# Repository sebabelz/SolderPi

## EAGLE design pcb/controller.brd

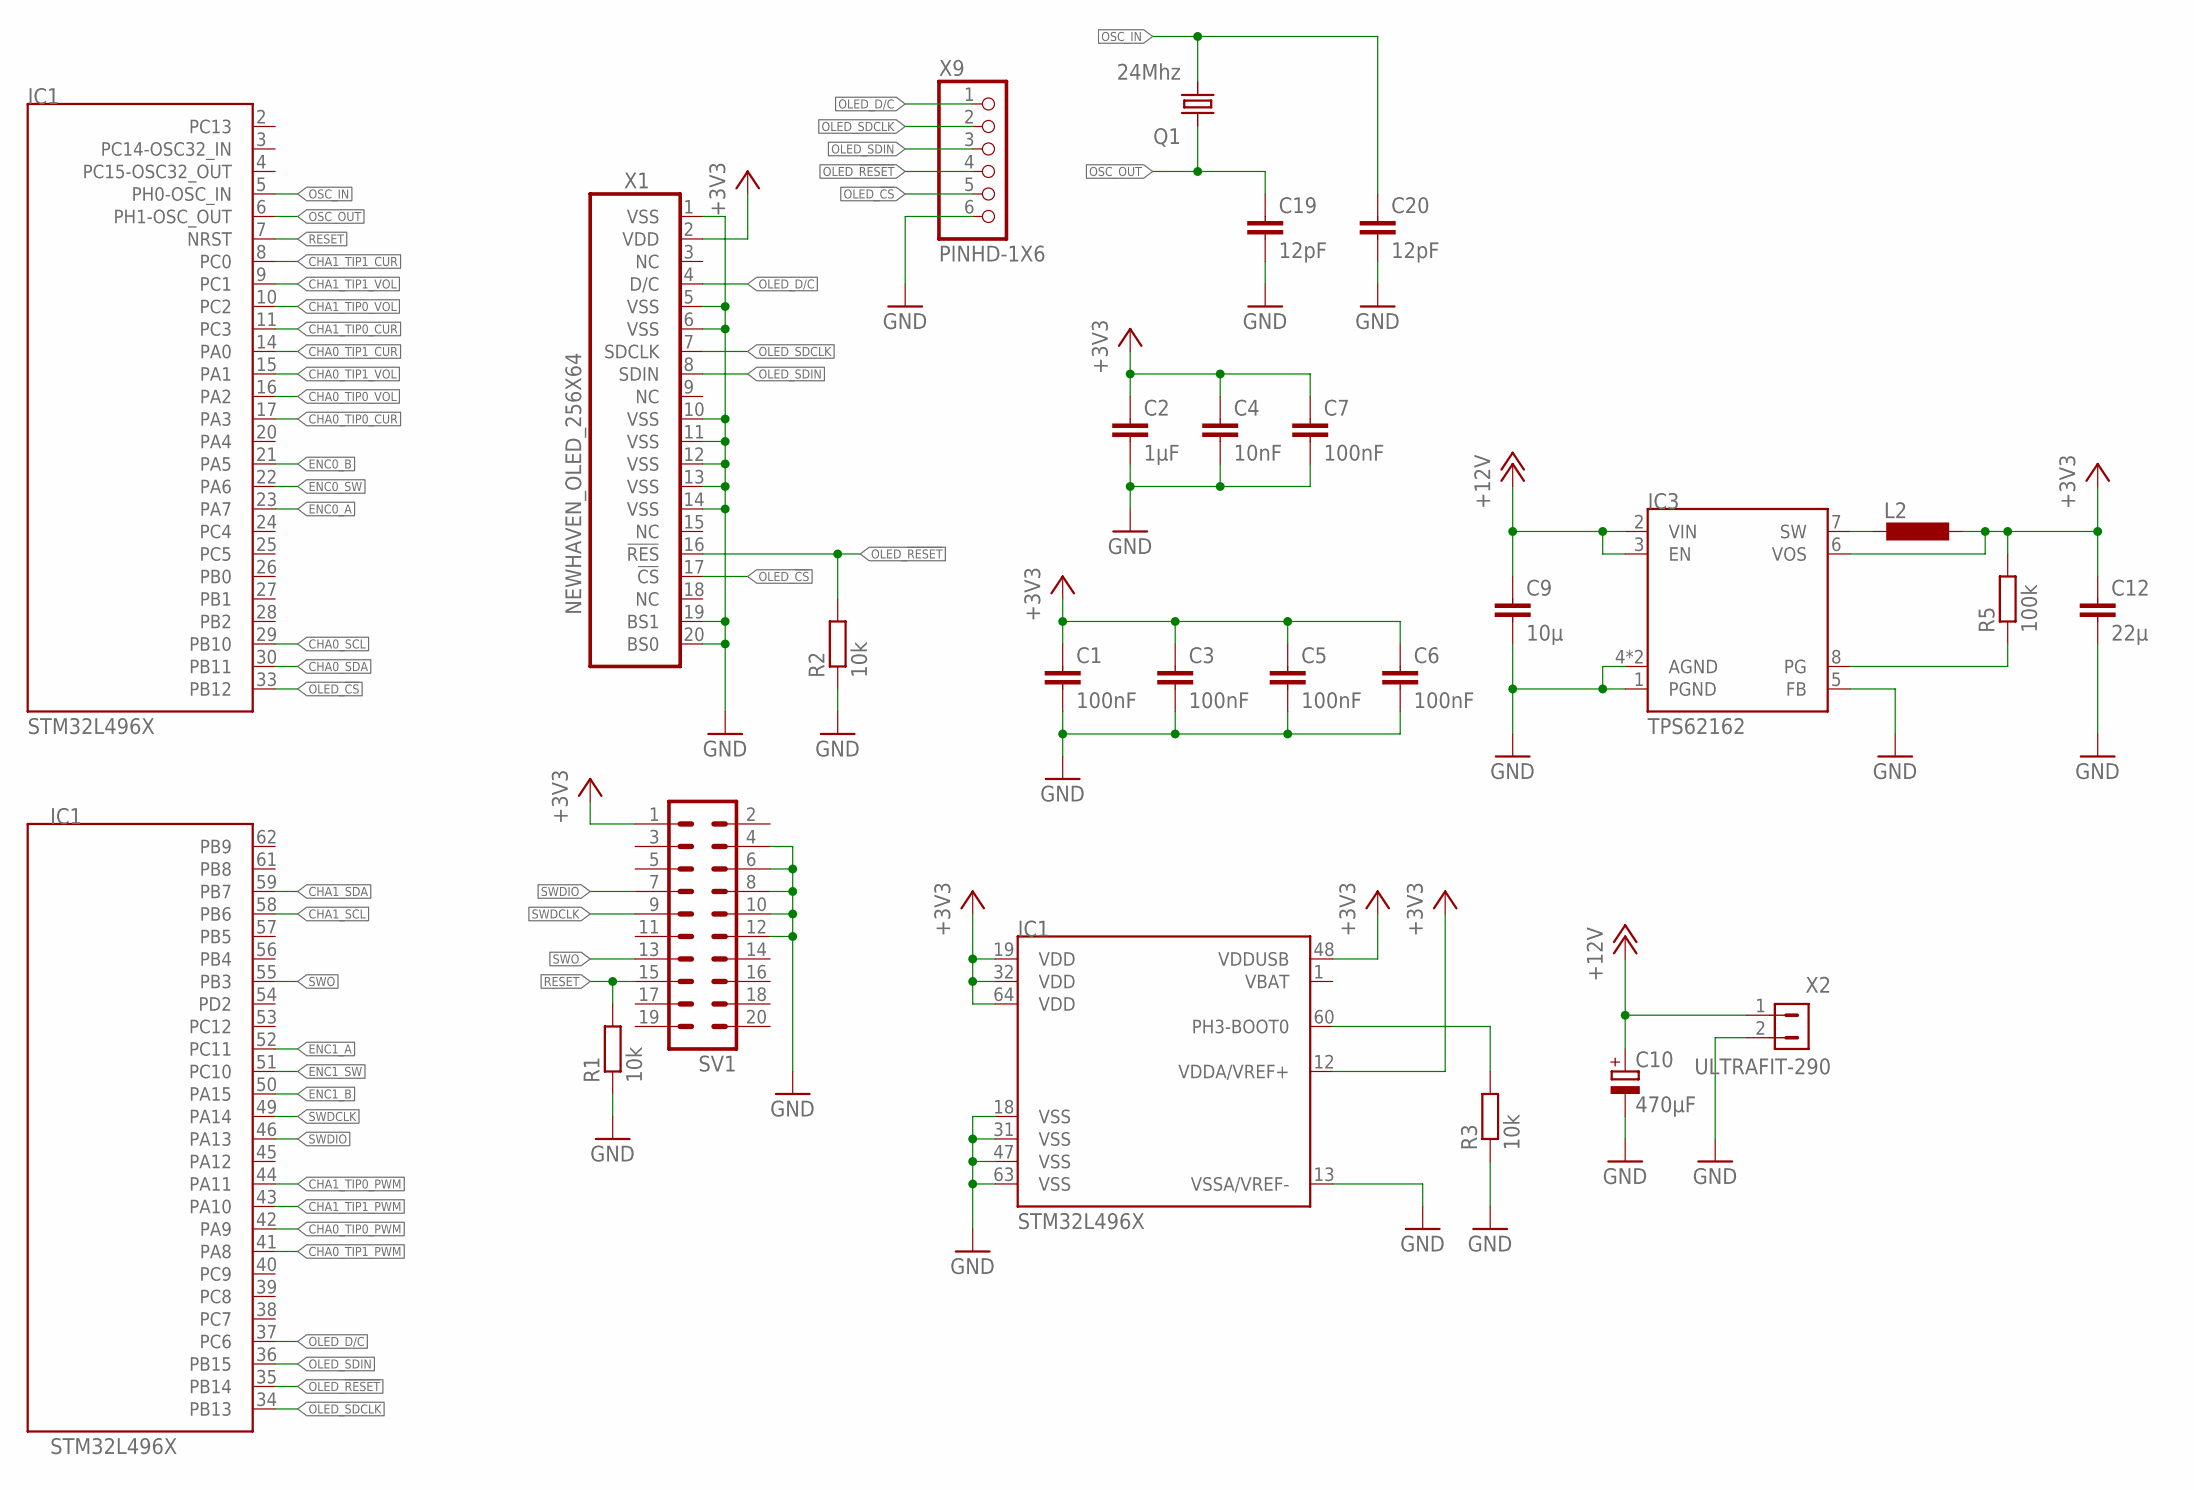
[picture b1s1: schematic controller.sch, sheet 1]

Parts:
C1, C3, C5, C6, C7: 100nF; C0402
C2: 1µF; C0402
C4: 10nF; C0402
C9: 10µ; C0805
C10: 470µF; C_EEEFK-10X10
C12: 22µ; C0805
C19, C20: 12pF; C0603
IC1: STM32L496X; TQFP64-10X10
IC3: TPS62162; WSON8
L2: VLF3012S; VLF3012ST
Q1: 24Mhz; HCR2520
R1, R2, R3: 10k; R0603
R5: 100k; R0603
SV1: ML20
X1: NEWHAVEN_OLED_256X64
X2: ULTRAFIT-290; ULTRAFIT-2-90
X9: PINHD-1X6; 1X06

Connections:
3V3_PG: IC3.8 (PG), R5.1
3V3_SW: IC3.7 (SW), L2.2
+3V3: C1.1, C2.1, C3.1, C4.1, C5.1, C6.1, C7.1, C12.1, IC1.12 (VDDA/VREF+), IC1.19 (VDD), IC1.32 (VDD), IC1.48 (VDDUSB), IC1.64 (VDD), IC3.6 (VOS), L2.1, R5.2, SV1.1, X1.2 (VDD); also elsewhere on the board
+12V: C9.1, C10.+, IC3.2 (VIN), IC3.3 (EN), X2.1; also elsewhere on the board
BOOT0: IC1.60 (PH3-BOOT0), R3.2
CHA0_SCL: IC1.29 (PB10); also elsewhere on the board
CHA0_SDA: IC1.30 (PB11); also elsewhere on the board
CHA0_TIP0_CUR: IC1.17 (PA3); also elsewhere on the board
CHA0_TIP0_PWM: IC1.42 (PA9); also elsewhere on the board
CHA0_TIP0_VOL: IC1.16 (PA2); also elsewhere on the board
CHA0_TIP1_CUR: IC1.14 (PA0); also elsewhere on the board
CHA0_TIP1_PWM: IC1.41 (PA8); also elsewhere on the board
CHA0_TIP1_VOL: IC1.15 (PA1); also elsewhere on the board
CHA1_SCL: IC1.58 (PB6); also elsewhere on the board
CHA1_SDA: IC1.59 (PB7); also elsewhere on the board
CHA1_TIP0_CUR: IC1.11 (PC3); also elsewhere on the board
CHA1_TIP0_PWM: IC1.44 (PA11); also elsewhere on the board
CHA1_TIP0_VOL: IC1.10 (PC2); also elsewhere on the board
CHA1_TIP1_CUR: IC1.8 (PC0); also elsewhere on the board
CHA1_TIP1_PWM: IC1.43 (PA10); also elsewhere on the board
CHA1_TIP1_VOL: IC1.9 (PC1); also elsewhere on the board
ENC0_A: IC1.23 (PA7); also elsewhere on the board
ENC0_B: IC1.21 (PA5); also elsewhere on the board
ENC0_SW: IC1.22 (PA6); also elsewhere on the board
ENC1_A: IC1.52 (PC11); also elsewhere on the board
ENC1_B: IC1.50 (PA15); also elsewhere on the board
ENC1_SW: IC1.51 (PC10); also elsewhere on the board
GND: C1.2, C2.2, C3.2, C4.2, C5.2, C6.2, C7.2, C9.2, C10.-, C12.2, C19.2, C20.2, IC1.13 (VSSA/VREF-), IC1.18 (VSS), IC1.31 (VSS), IC1.47 (VSS), IC1.63 (VSS), IC3.1 (PGND), IC3.4 (AGND), IC3.5 (FB), IC3.GND (AGND), R1.1, R2.1, R3.1, SV1.4, SV1.6, SV1.8, SV1.10, SV1.12, X1.1 (VSS), X1.5 (VSS), X1.6 (VSS), X1.10 (VSS), X1.11 (VSS), X1.12 (VSS), X1.13 (VSS), X1.14 (VSS), X1.19 (BS1), X1.20 (BS0), X2.2, X9.6; also elsewhere on the board
OLED_!CS: IC1.33 (PB12), X1.17 (!CS), X9.5
OLED_!RESET: IC1.35 (PB14), R2.2, X1.16 (!RES), X9.4
OLED_D/C: IC1.37 (PC6), X1.4 (D/C), X9.1
OLED_SDCLK: IC1.34 (PB13), X1.7 (SDCLK), X9.2
OLED_SDIN: IC1.36 (PB15), X1.8 (SDIN), X9.3
OSC_IN: C20.1, IC1.5 (PH0-OSC_IN), Q1.1
OSC_OUT: C19.1, IC1.6 (PH1-OSC_OUT), Q1.2
RESET: IC1.7 (NRST), R1.2, SV1.15
SWDCLK: IC1.49 (PA14), SV1.9
SWDIO: IC1.46 (PA13), SV1.7
SWO: IC1.55 (PB3), SV1.13

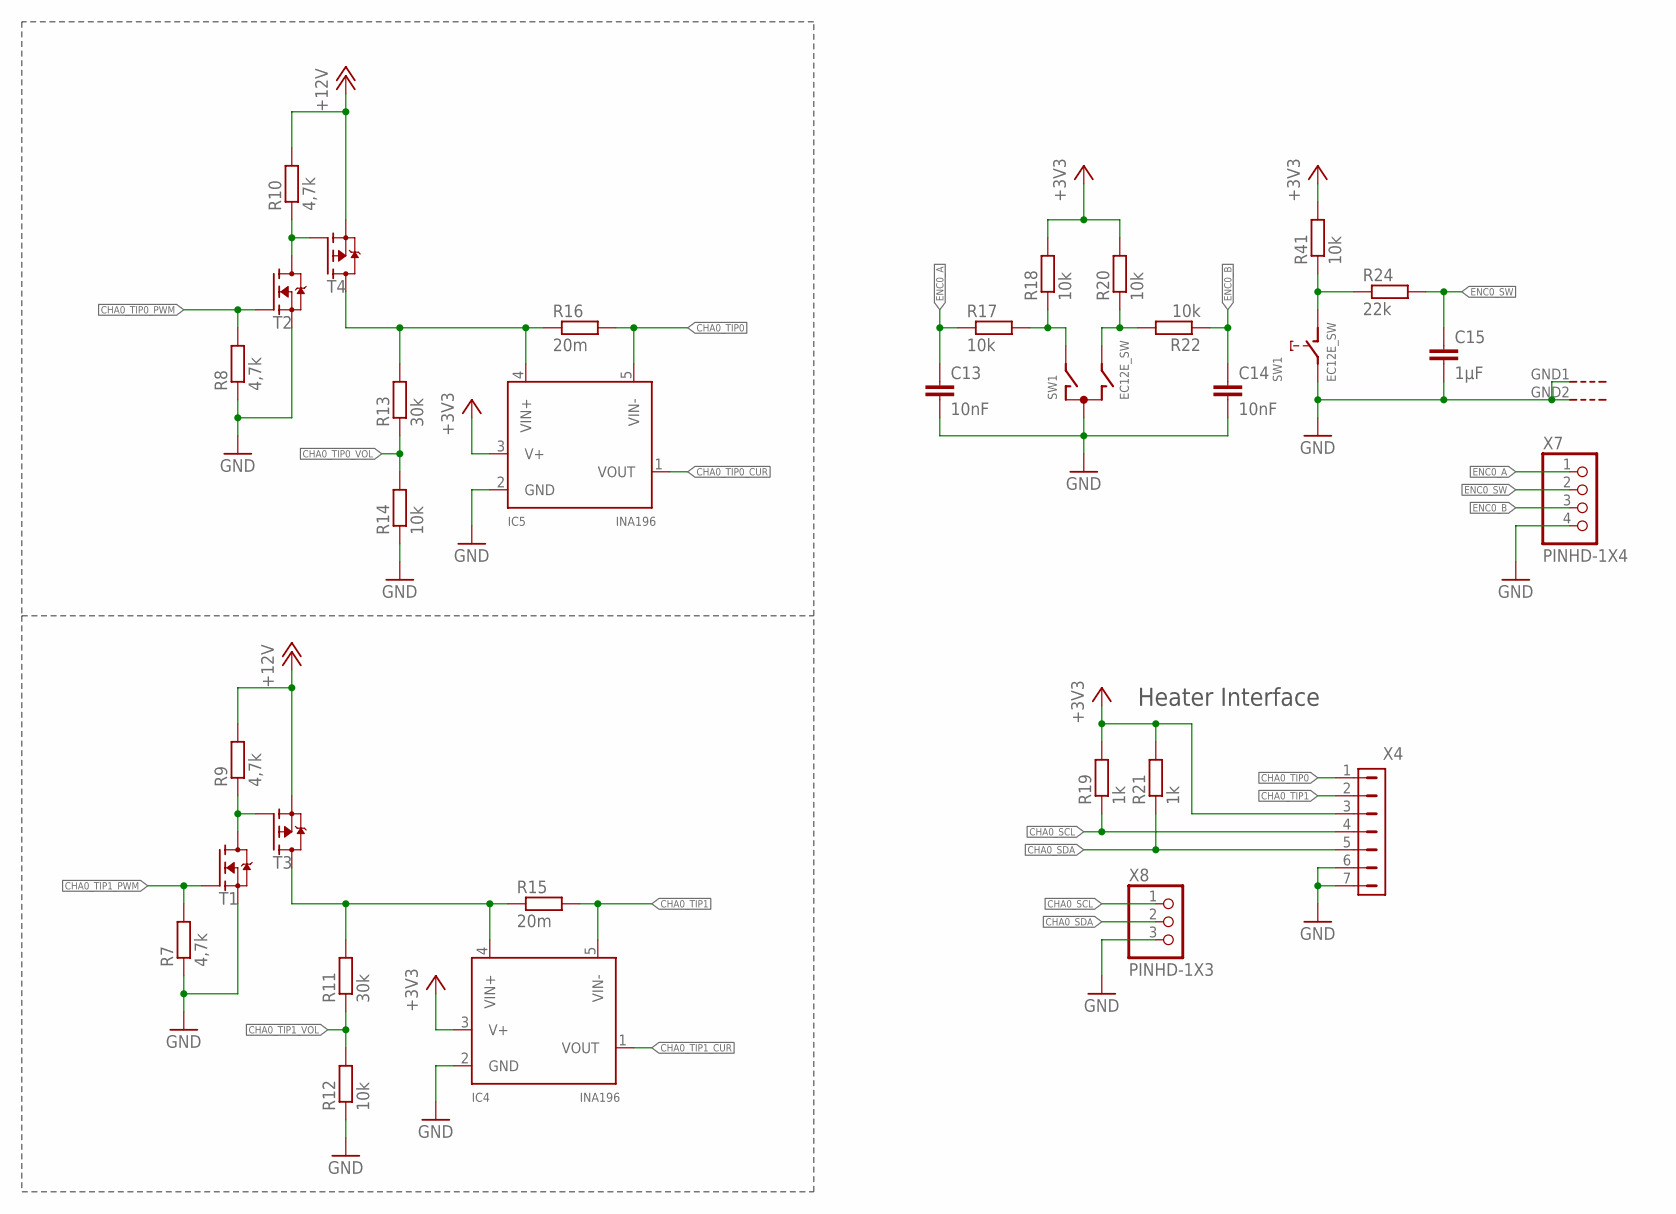
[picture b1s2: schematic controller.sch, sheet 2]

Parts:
C13, C14: 10nF; C0805
C15: 1µF; C0805
IC4, IC5: INA196; SOT23-5L
R7, R8, R9, R10: 4,7k; R0805
R11, R13: 30k; R0603
R12, R14: 10k; R0603
R15, R16: 20m; R2010
R17, R18, R20, R22, R41: 10k; R0805
R19, R21: 1k; R0603
R24: 22k; R0805
SW1: EC12E_SW; ALPS_EC12E_SW
T1, T2: NVR4003NT3G; SOT23
T3, T4: IRF7416; SO8
X4: NANOFIT-7
X7: PINHD-1X4; 1X04
X8: PINHD-1X3; 1X03

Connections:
+3V3: IC4.3 (V+), IC5.3 (V+), R18.2, R19.2, R20.2, R21.2, R41.2, X4.3; also elsewhere on the board
+12V: R9.2, R10.2, T3.1 (S), T3.2 (S), T3.3 (S), T4.1 (S), T4.2 (S), T4.3 (S); also elsewhere on the board
CHA0_SCL: R19.1, X4.4, X8.1; also elsewhere on the board
CHA0_SDA: R21.1, X4.5, X8.2; also elsewhere on the board
CHA0_TIP0: IC5.5 (VIN-), R16.2, X4.1
CHA0_TIP0_CUR: IC5.1 (VOUT); also elsewhere on the board
CHA0_TIP0_PWM: R8.2, T2.1 (G); also elsewhere on the board
CHA0_TIP0_PWM_D: R10.1, T2.3 (D), T4.4 (G)
CHA0_TIP0_SEN: IC5.4 (VIN+), R13.2, R16.1, T4.5 (D), T4.6 (D), T4.7 (D), T4.8 (D)
CHA0_TIP0_VOL: R13.1, R14.2; also elsewhere on the board
CHA0_TIP1: IC4.5 (VIN-), R15.2, X4.2
CHA0_TIP1_CUR: IC4.1 (VOUT); also elsewhere on the board
CHA0_TIP1_PWM: R7.2, T1.1 (G); also elsewhere on the board
CHA0_TIP1_PWM_D: R9.1, T1.3 (D), T3.4 (G)
CHA0_TIP1_SEN: IC4.4 (VIN+), R11.2, R15.1, T3.5 (D), T3.6 (D), T3.7 (D), T3.8 (D)
CHA0_TIP1_VOL: R11.1, R12.2; also elsewhere on the board
ENC0_A: C13.1, R17.1, X7.1; also elsewhere on the board
ENC0_A_UNFIL: R17.2, R18.1, SW1.A
ENC0_B: C14.1, R22.1, X7.3; also elsewhere on the board
ENC0_B_UNFIL: R20.1, R22.2, SW1.B
ENC0_SW: C15.1, R24.2, X7.2; also elsewhere on the board
ENC0_SW_R: R24.1, R41.1, SW1.D (1)
GND: C13.2, C14.2, C15.2, IC4.2 (GND), IC5.2 (GND), R7.1, R8.1, R12.1, R14.1, SW1.C, SW1.E (2), SW1.GND1 (G), SW1.GND2 (G), T1.2 (S), T2.2 (S), X4.6, X4.7, X7.4, X8.3; also elsewhere on the board

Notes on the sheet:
Heater Interface

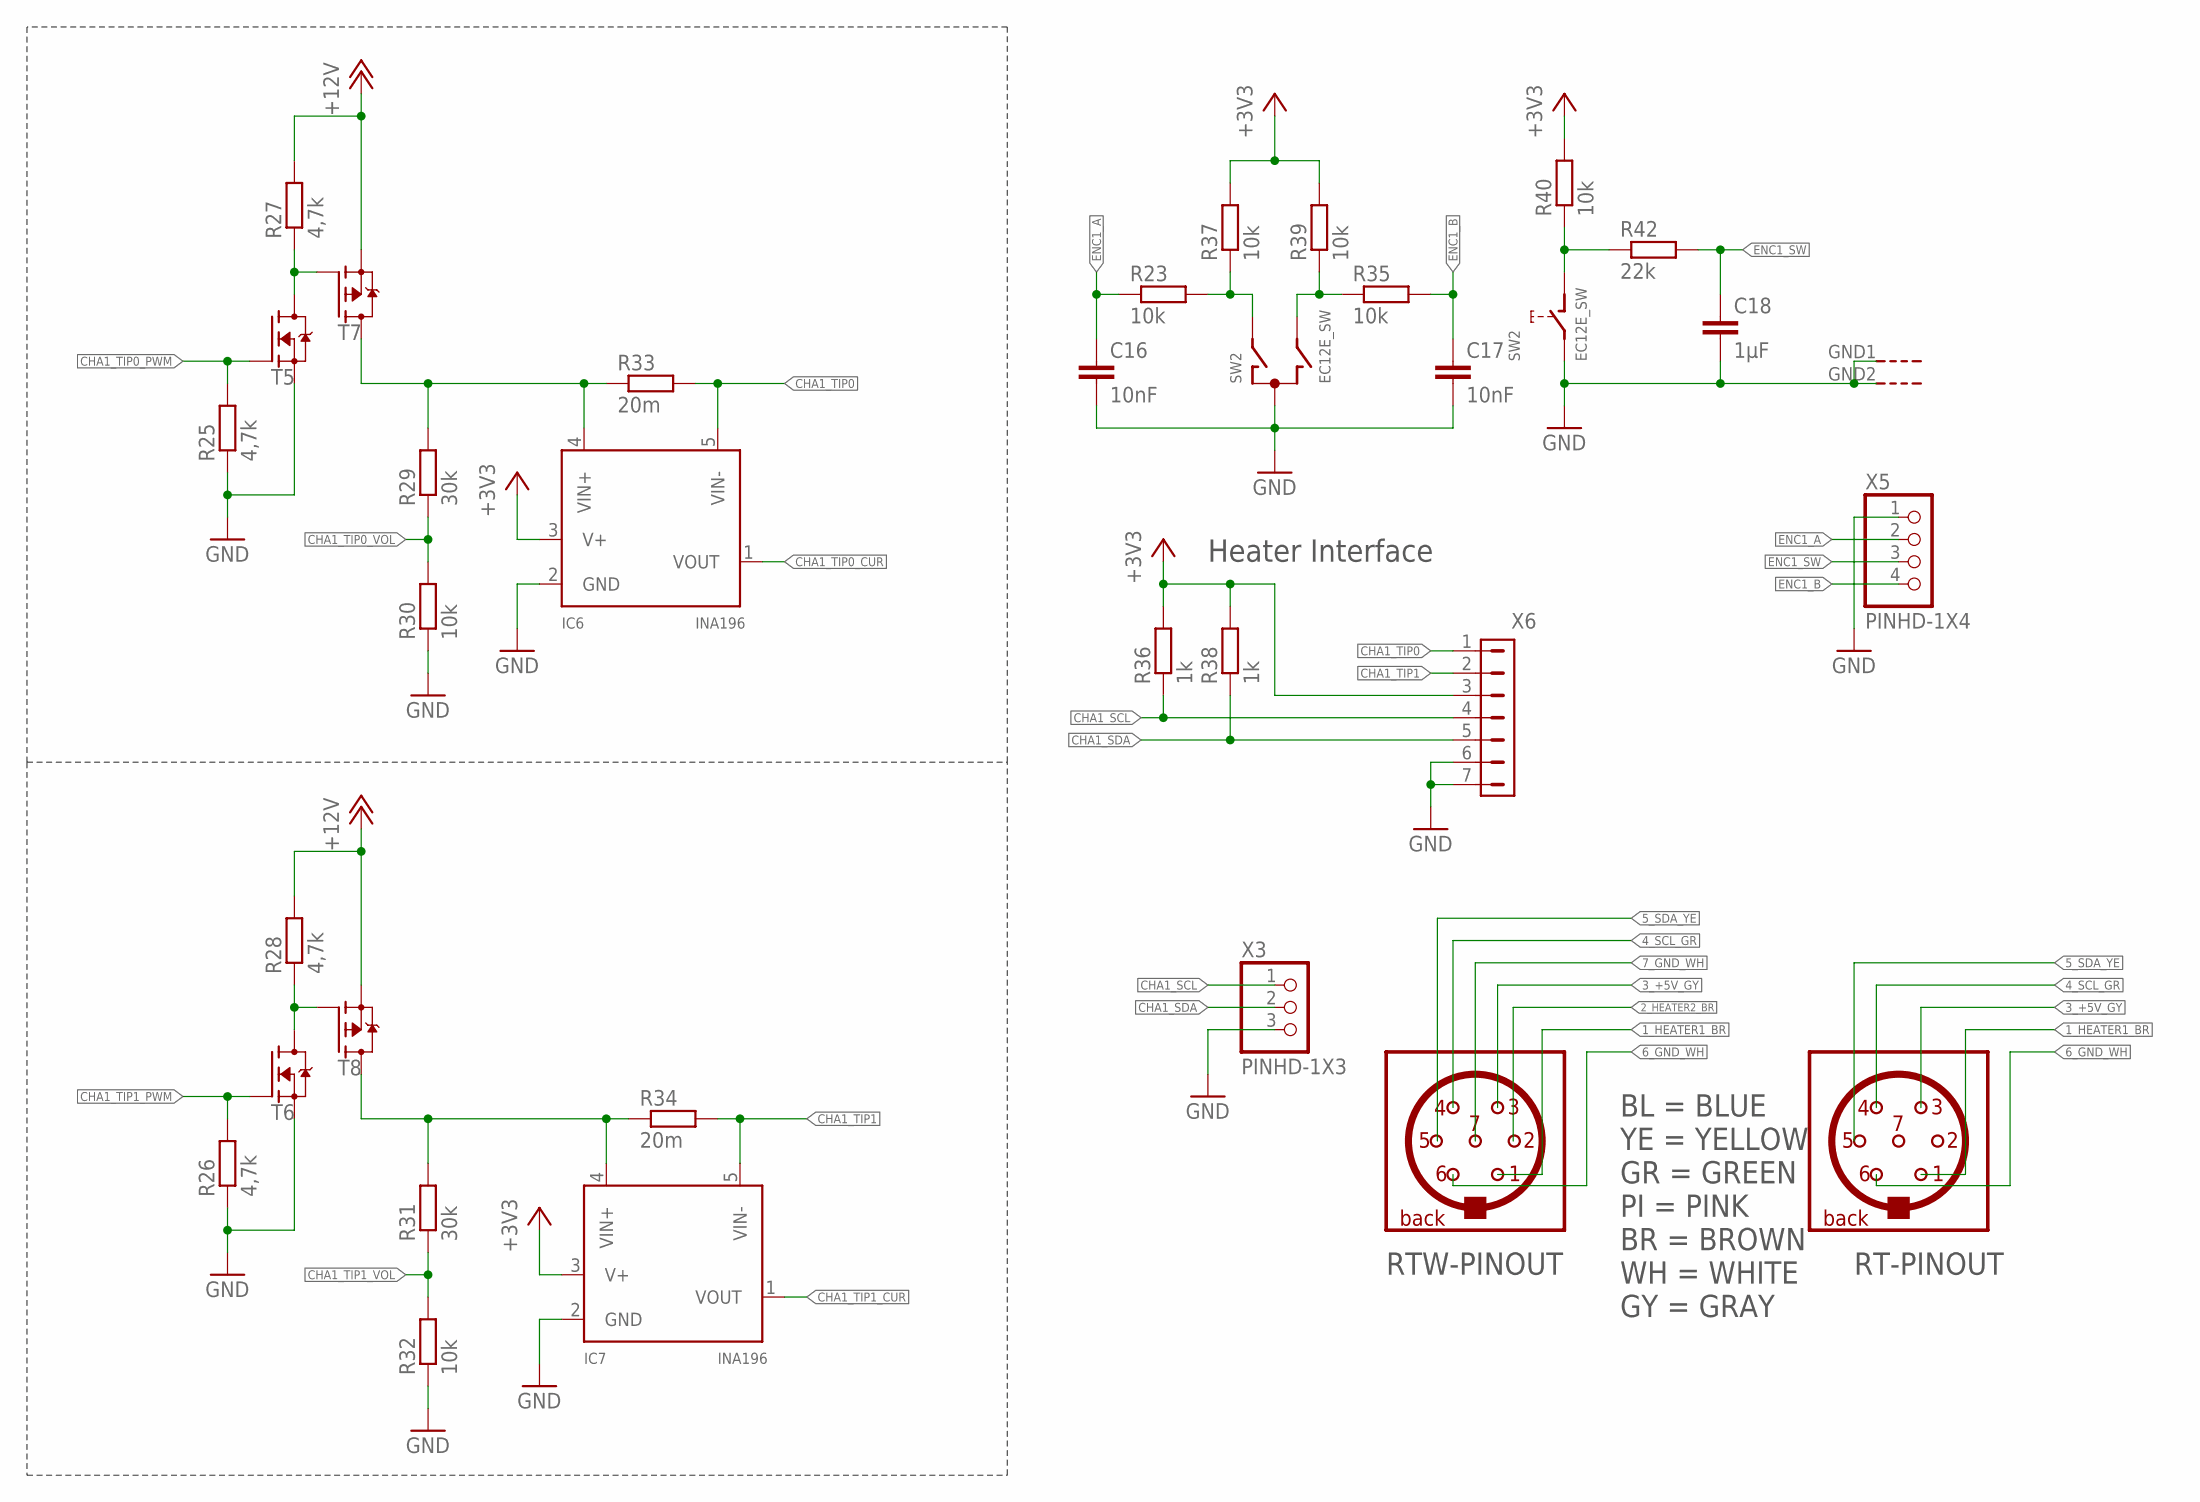
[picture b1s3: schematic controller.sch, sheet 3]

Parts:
C16, C17: 10nF; C0805
C18: 1µF; C0805
IC6, IC7: INA196; SOT23-5L
R23, R35, R37, R39, R40: 10k; R0805
R25, R26, R27, R28: 4,7k; R0805
R29, R31: 30k; R0603
R30, R32: 10k; R0603
R33, R34: 20m; R2010
R36, R38: 1k; R0603
R42: 22k; R0805
SW2: EC12E_SW; ALPS_EC12E_SW
T5, T6: NVR4003NT3G; SOT23
T7, T8: IRF7416; SO8
X3: PINHD-1X3; 1X03
X5: PINHD-1X4; 1X04
X6: NANOFIT-7

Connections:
+3V3: IC6.3 (V+), IC7.3 (V+), R36.2, R37.2, R38.2, R39.2, R40.2, X6.3; also elsewhere on the board
+12V: R27.2, R28.2, T7.1 (S), T7.2 (S), T7.3 (S), T8.1 (S), T8.2 (S), T8.3 (S); also elsewhere on the board
CHA1_SCL: R36.1, X3.1, X6.4; also elsewhere on the board
CHA1_SDA: R38.1, X3.2, X6.5; also elsewhere on the board
CHA1_TIP0: IC6.5 (VIN-), R33.2, X6.1
CHA1_TIP0_CUR: IC6.1 (VOUT); also elsewhere on the board
CHA1_TIP0_PWM: R25.2, T5.1 (G); also elsewhere on the board
CHA1_TIP0_PWM_D: R27.1, T5.3 (D), T7.4 (G)
CHA1_TIP0_SEN: IC6.4 (VIN+), R29.2, R33.1, T7.5 (D), T7.6 (D), T7.7 (D), T7.8 (D)
CHA1_TIP0_VOL: R29.1, R30.2; also elsewhere on the board
CHA1_TIP1: IC7.5 (VIN-), R34.2, X6.2
CHA1_TIP1_CUR: IC7.1 (VOUT); also elsewhere on the board
CHA1_TIP1_PWM: R26.2, T6.1 (G); also elsewhere on the board
CHA1_TIP1_PWM_D: R28.1, T6.3 (D), T8.4 (G)
CHA1_TIP1_SEN: IC7.4 (VIN+), R31.2, R34.1, T8.5 (D), T8.6 (D), T8.7 (D), T8.8 (D)
CHA1_TIP1_VOL: R31.1, R32.2; also elsewhere on the board
ENC1_A: C16.1, R23.1, X5.2; also elsewhere on the board
ENC1_A_UNFIL: R23.2, R37.1, SW2.A
ENC1_B: C17.1, R35.2, X5.4; also elsewhere on the board
ENC1_B_UNFIL: R35.1, R39.1, SW2.B
ENC1_SW: C18.1, R42.2, X5.3; also elsewhere on the board
ENC1_SW_R: R40.1, R42.1, SW2.D (1)
GND: C16.2, C17.2, C18.2, IC6.2 (GND), IC7.2 (GND), R25.1, R26.1, R30.1, R32.1, SW2.C, SW2.E (2), SW2.GND1 (G), SW2.GND2 (G), T5.2 (S), T6.2 (S), X3.3, X5.1, X6.6, X6.7; also elsewhere on the board

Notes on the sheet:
Heater Interface
BL = BLUE YE = YELLOW GR = GREEN PI = PINK BR = BROWN WH = WHITE GY = GRAY
RTW-PINOUT
RT-PINOUT

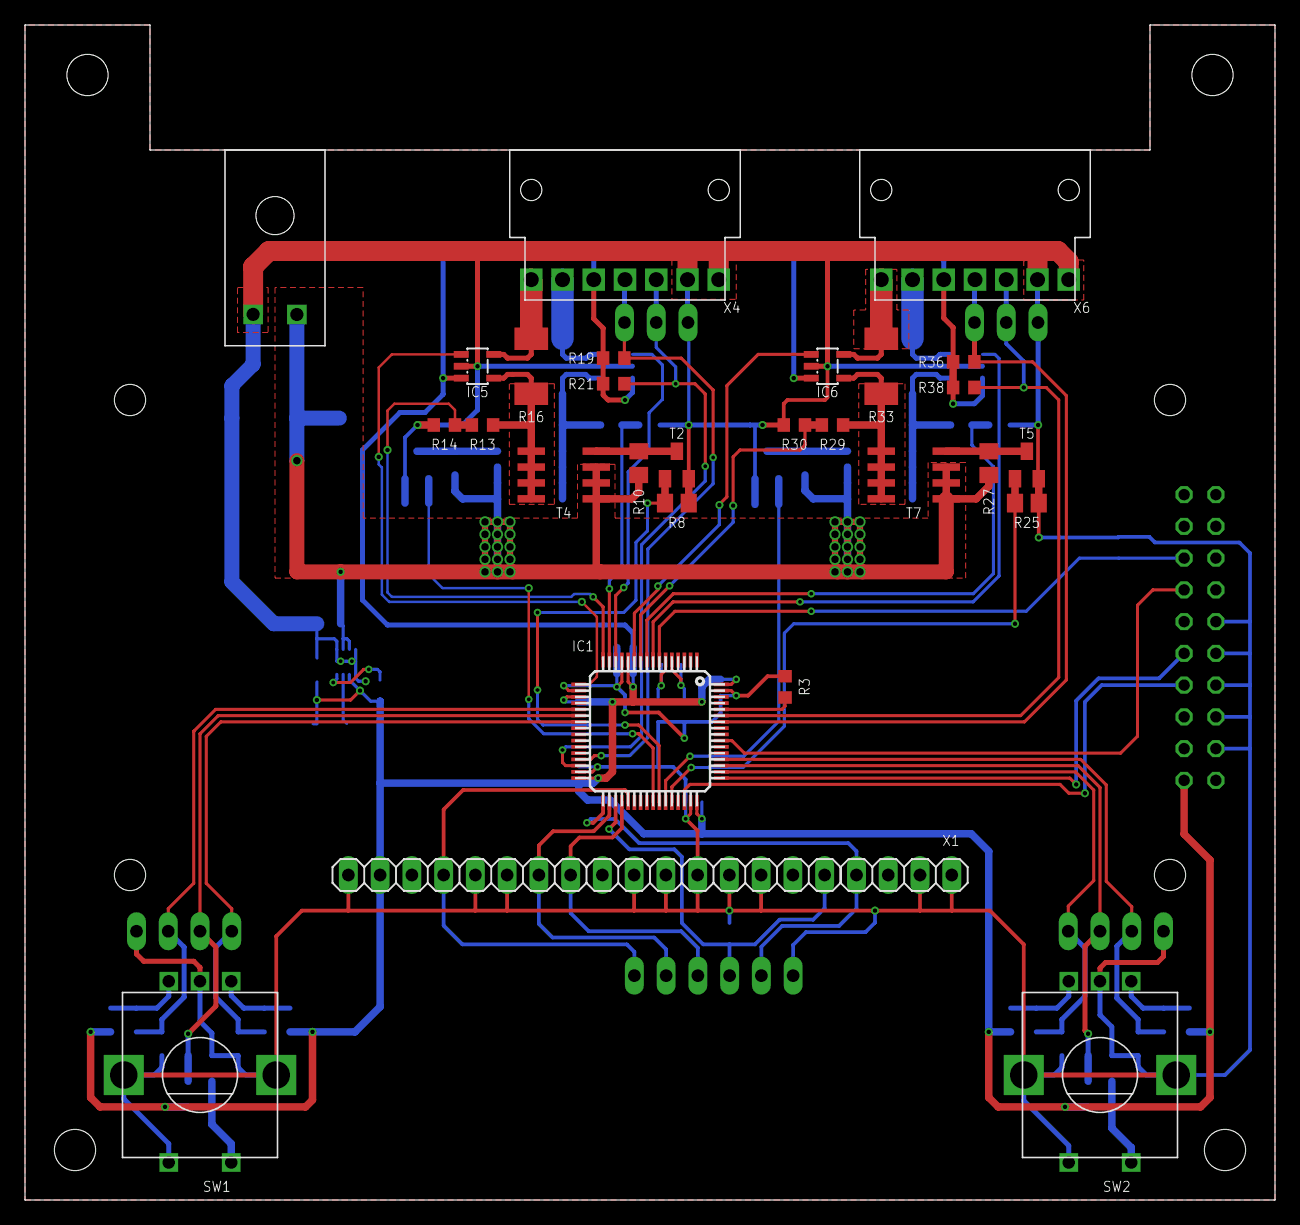
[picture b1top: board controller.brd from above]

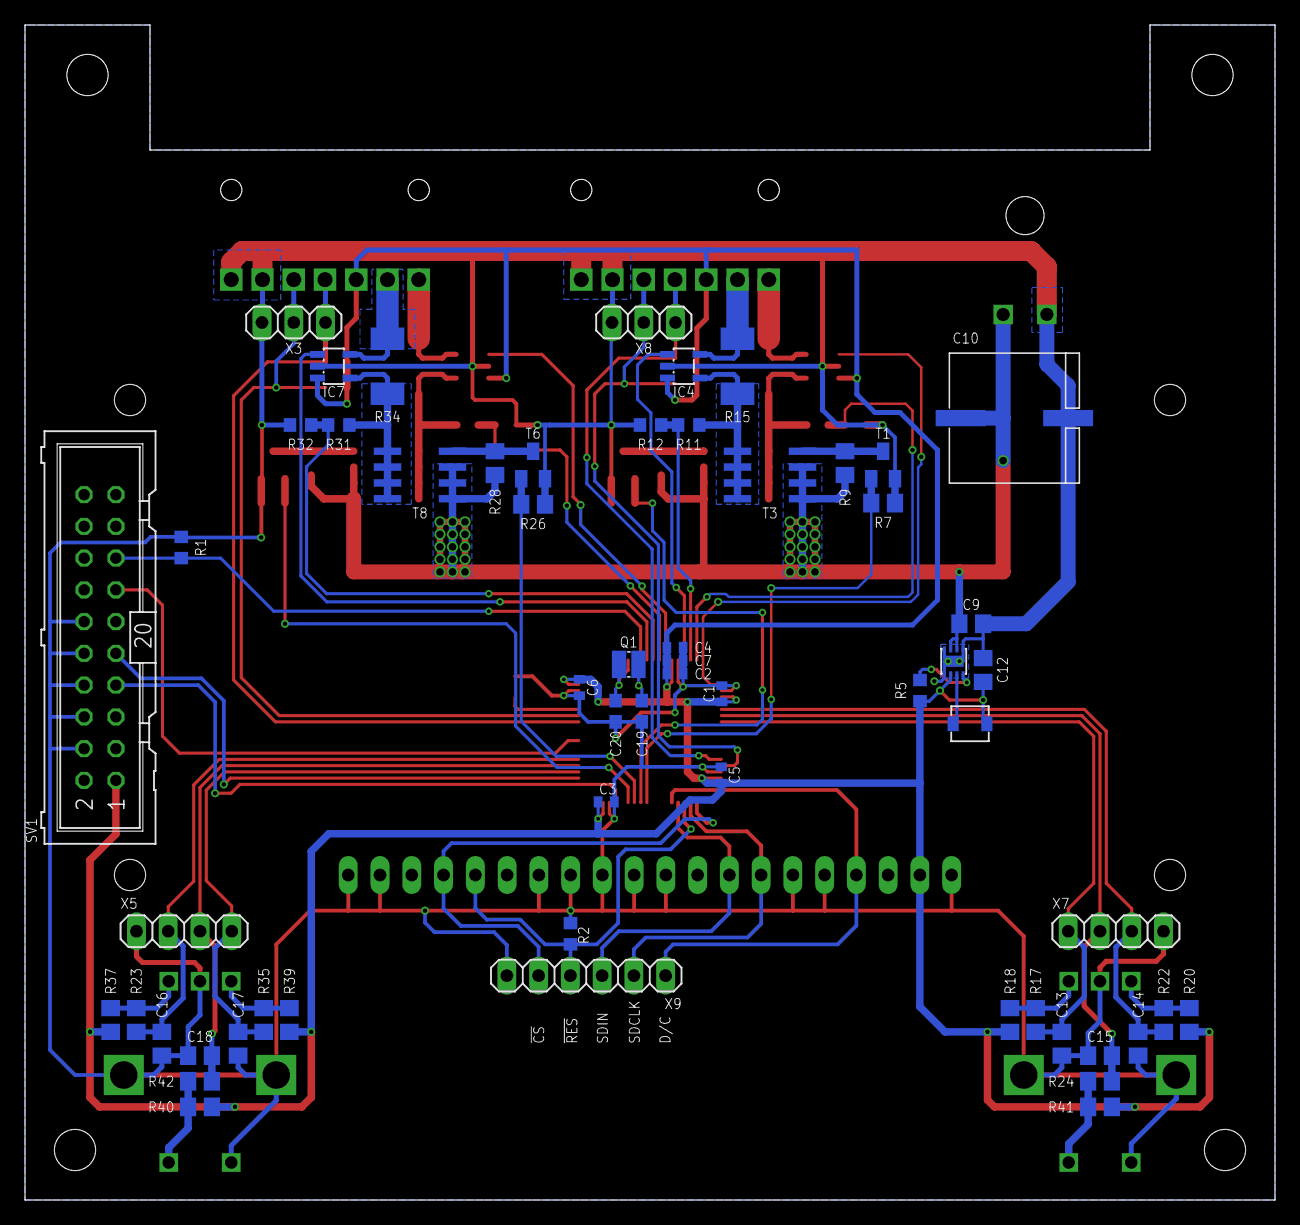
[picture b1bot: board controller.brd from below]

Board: 2 copper layers, 100.0 x 94.0 mm, 86 parts (58 on the bottom side), 57 nets.

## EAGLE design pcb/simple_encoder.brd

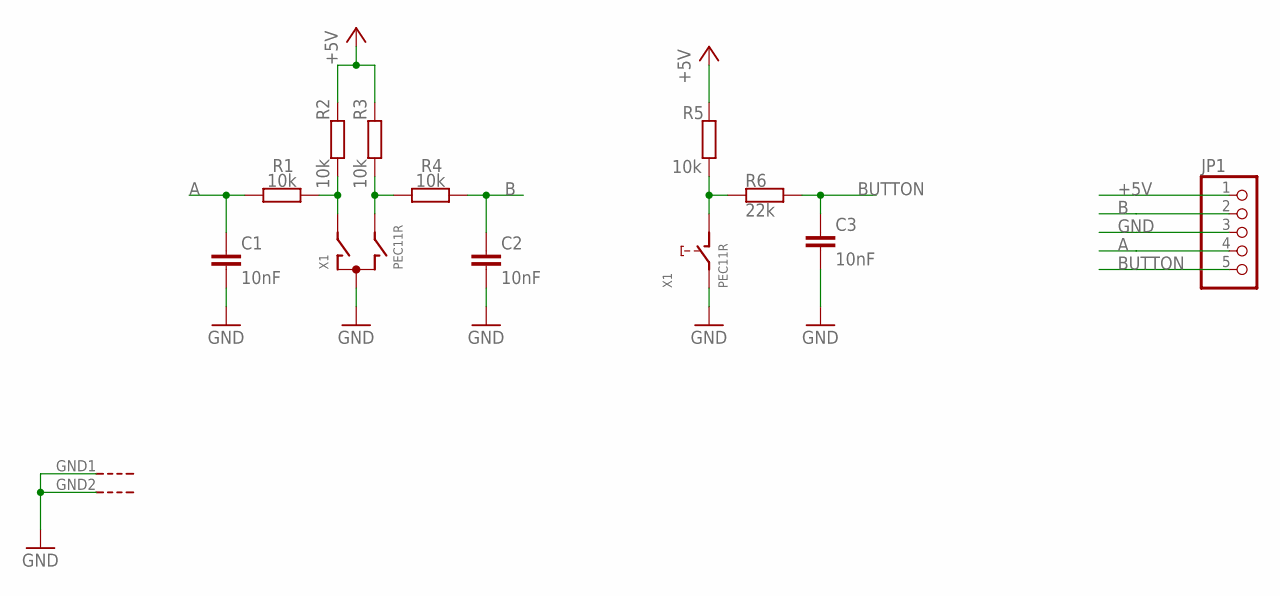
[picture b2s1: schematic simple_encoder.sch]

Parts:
C1, C2, C3: 10nF; C0805
JP1: PINHD-1X5; 1X05
R1, R2, R3, R4, R5: 10k; R0805
R6: 22k; R0805
X1: PEC11R

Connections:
+5V: JP1.1, R2.2, R3.2, R5.2
A: C1.1, JP1.4, R1.1
A_UNFIL: R1.2, R2.1, X1.A
B: C2.1, JP1.2, R4.2
BUTTON: C3.1, JP1.5, R6.2
BUTTON_UNFIL: R5.1, R6.1, X1.D
B_UNFIL: R3.1, R4.1, X1.B
GND: C1.2, C2.2, C3.2, JP1.3, X1.C, X1.E, X1.GND1 (G), X1.GND2 (G)

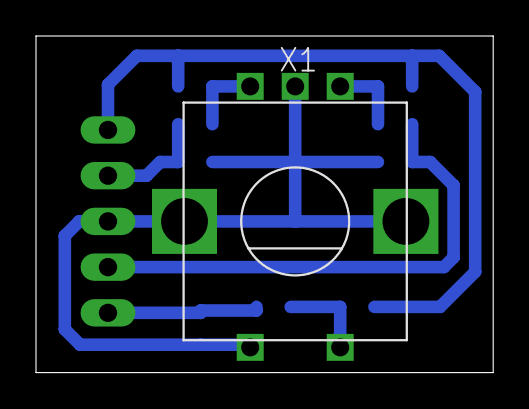
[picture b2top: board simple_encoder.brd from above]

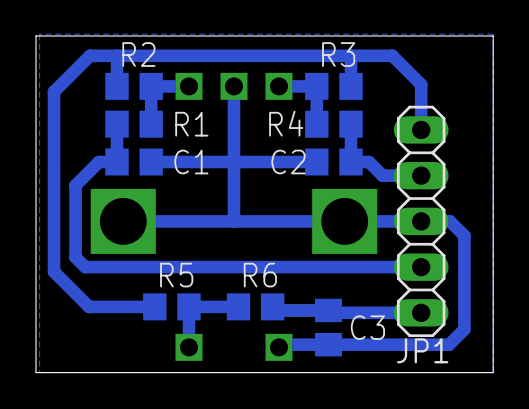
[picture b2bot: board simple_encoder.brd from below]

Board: 2 copper layers, 25.4 x 18.7 mm, 11 parts (10 on the bottom side), 8 nets.

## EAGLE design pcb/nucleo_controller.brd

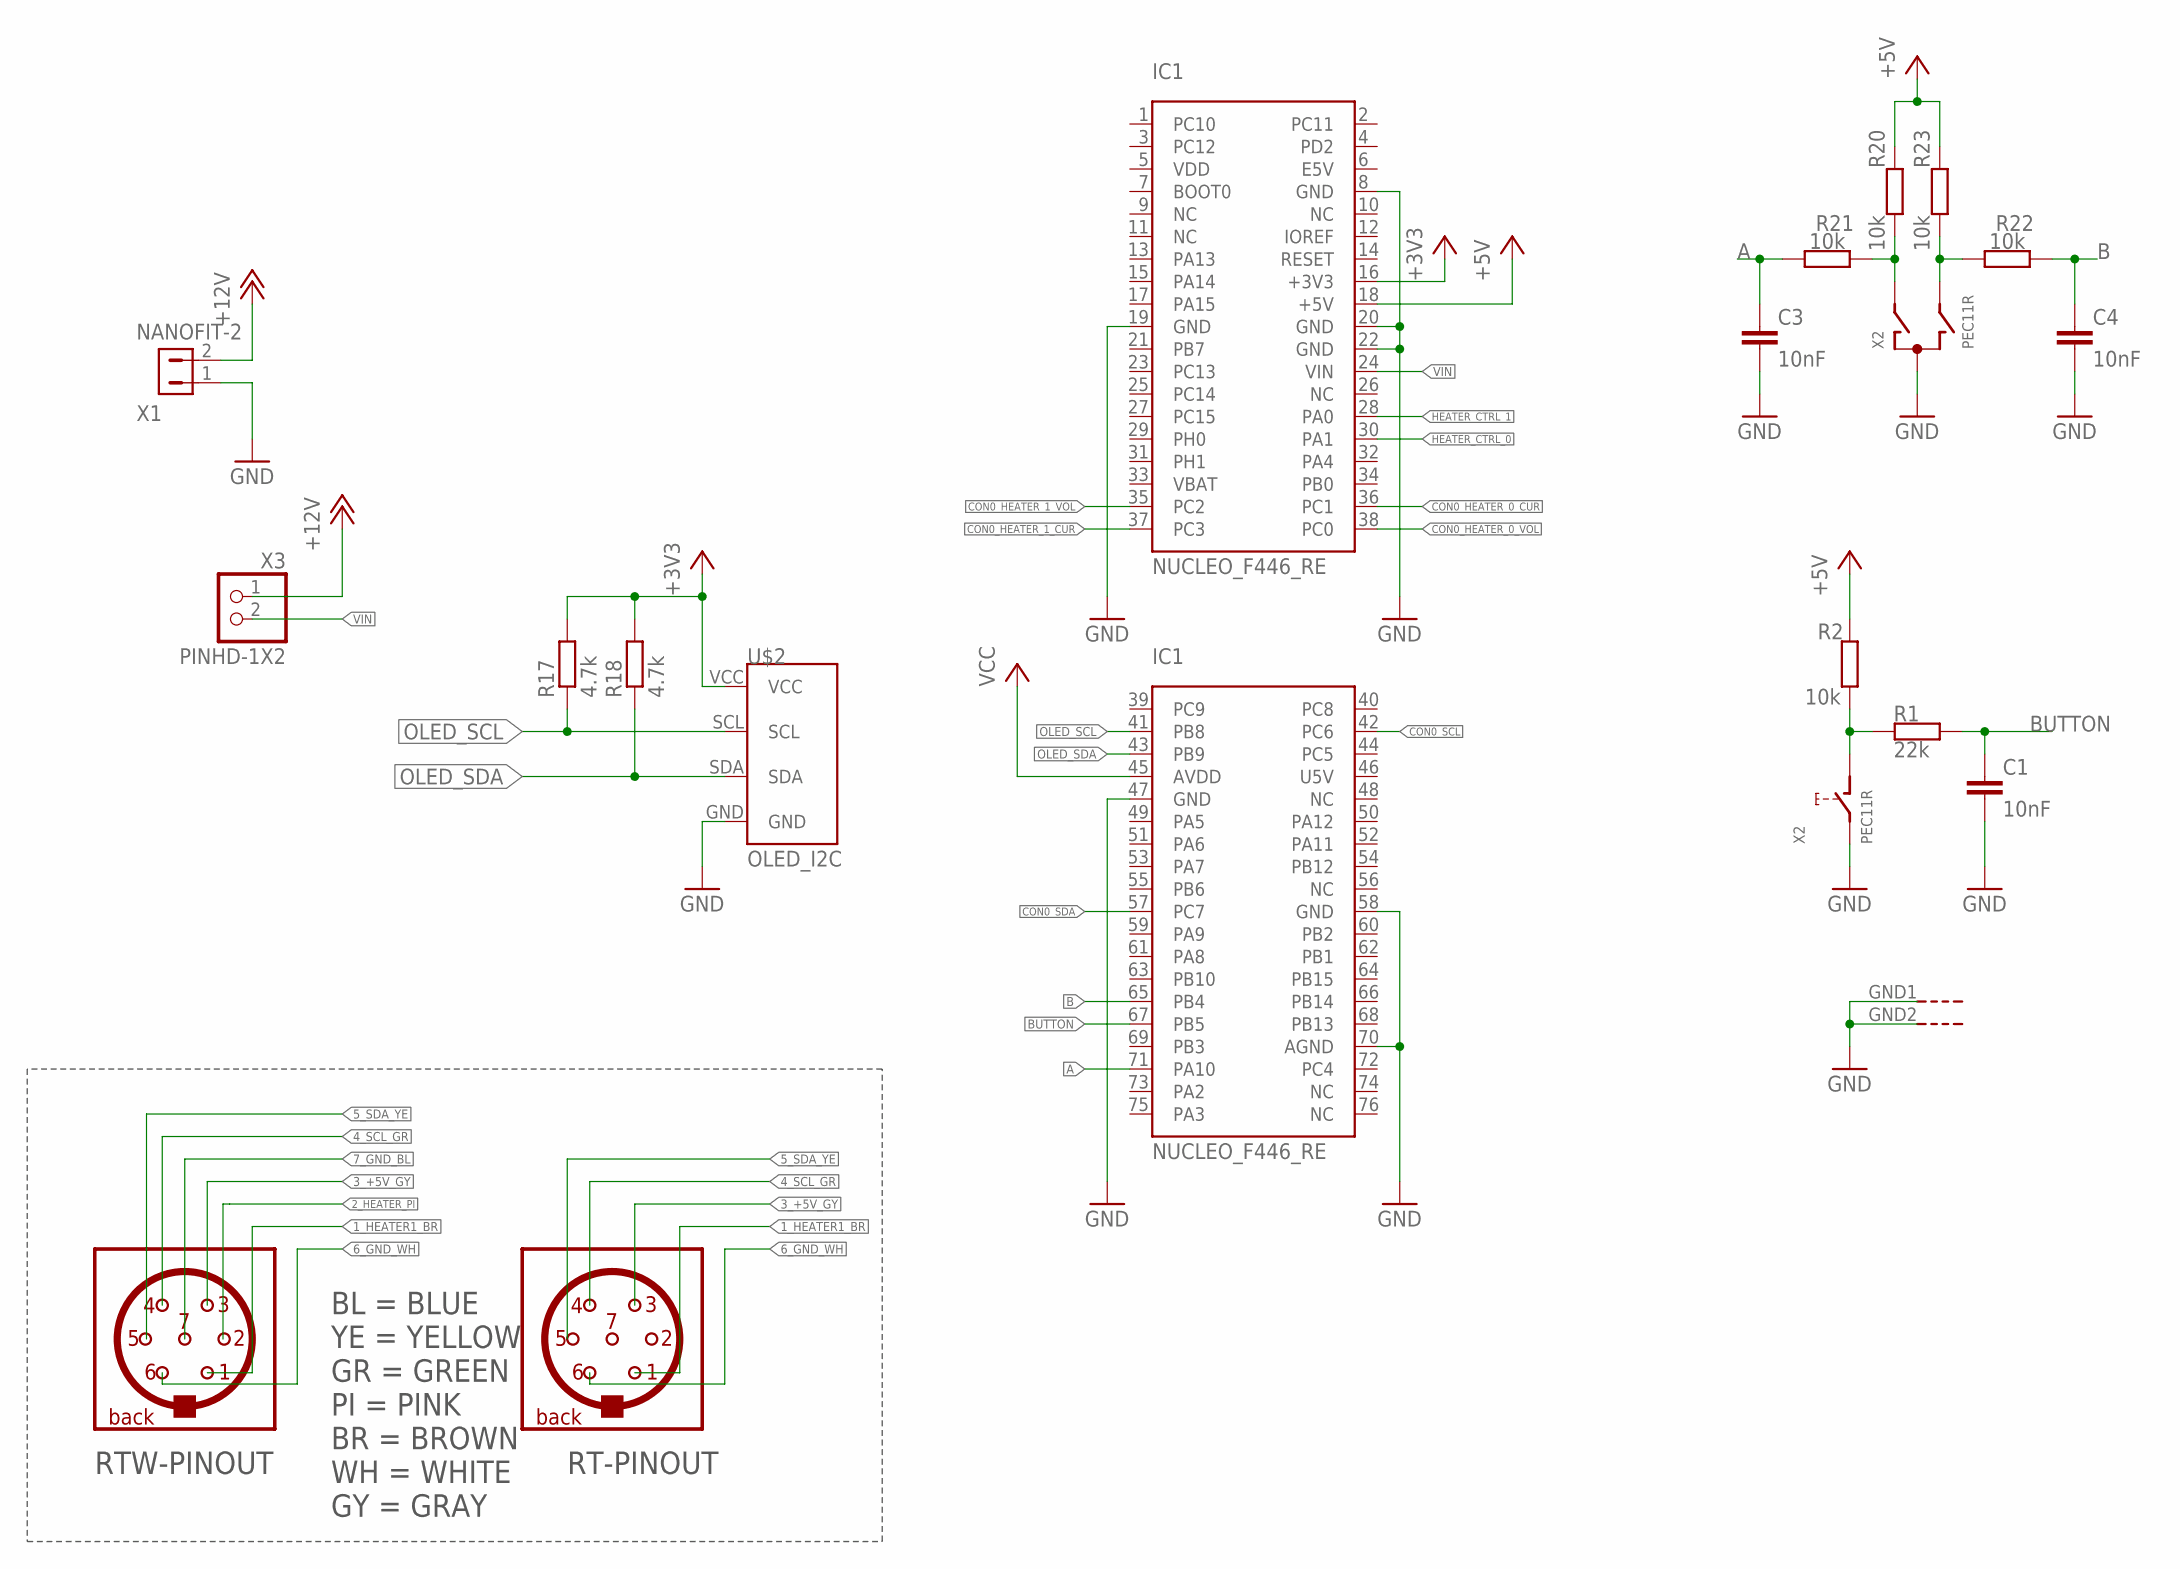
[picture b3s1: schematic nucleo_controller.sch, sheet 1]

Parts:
C1, C3, C4: 10nF; C0805
IC1: NUCLEO_F446_RE
R1: 22k; R0805
R2, R20, R21, R22, R23: 10k; R0805
R17, R18: 4.7k; R0603
U$2: OLED_I2C
X1: NANOFIT-2; NANOFIT-2-90
X2: PEC11R
X3: PINHD-1X2; 1X02

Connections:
+3V3: IC1.16 (+3V3), R17.2, R18.2, U$2.VCC
+5V: IC1.18 (+5V), R2.2, R20.2, R23.2; also elsewhere on the board
+12V: X1.2, X3.1; also elsewhere on the board
A: C3.1, IC1.71 (PA10), R21.1
A_UNFIL: R20.1, R21.2, X2.A
B: C4.1, IC1.65 (PB4), R22.2
BUTTON: C1.1, IC1.67 (PB5), R1.2
BUTTON_UNFIL: R1.1, R2.1, X2.D
B_UNFIL: R22.1, R23.1, X2.B
CON0_HEATER_0_CUR: IC1.36 (PC1); also elsewhere on the board
CON0_HEATER_0_VOL: IC1.38 (PC0); also elsewhere on the board
CON0_HEATER_1_CUR: IC1.37 (PC3); also elsewhere on the board
CON0_HEATER_1_VOL: IC1.35 (PC2); also elsewhere on the board
CON0_SCL: IC1.42 (PC6); also elsewhere on the board
CON0_SDA: IC1.57 (PC7); also elsewhere on the board
GND: C1.2, C3.2, C4.2, IC1.8 (GND), IC1.19 (GND), IC1.20 (GND), IC1.22 (GND), IC1.47 (GND), IC1.58 (GND), IC1.70 (AGND), U$2.GND, X1.1, X2.C, X2.E, X2.GND1 (G), X2.GND2 (G); also elsewhere on the board
HEATER_CTRL_0: IC1.30 (PA1); also elsewhere on the board
HEATER_CTRL_1: IC1.28 (PA0); also elsewhere on the board
OLED_SCL: IC1.41 (PB8), R17.1, U$2.SCL
OLED_SDA: IC1.43 (PB9), R18.1, U$2.SDA
VCC: IC1.45 (AVDD); also elsewhere on the board
VIN: IC1.24 (VIN), X3.2

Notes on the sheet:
BL = BLUE YE = YELLOW GR = GREEN PI = PINK BR = BROWN WH = WHITE GY = GRAY
RTW-PINOUT
RT-PINOUT
